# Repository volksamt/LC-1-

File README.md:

# LC-1-
Schematics for LC1 (Loud Card 1) miniature synthesizer/trigger generator

<h2> Copy </h2>
LC-1 is an armament designed to turn you into an Artiste-Agitator.

With its compact build, highly variable frequency range, and ferocious output power of 3Vpp, LC-1 is the perfect sonic infiltration tool
 for jam sessions and free-improvisation ensembles alike. 

It is crafted in alignment with Volksamt!’s artistic manifesto;

*
Hierarchy and harmony are shackles unto everything!
FcCUk order!
*

However, 
it would be absurd to send you to the fronts without sufficient training.
Thus;
 in the following pages you will find various scores
designed to boost your acumen.
Rehearse these well.

<h2> Technical </h2>

Lc1 is a mini touch reactive synthesizer designed as a small scale version of the much bigger light&sound installation |||||||| (wwww.volksamt.org/menagerie.html)

It is built around a simple schmitt trigger feedback oscillator design. 

Feel free to experiment with the capacitor values as everybodies skin resistance is different. Usually 22nF is a good stating point.

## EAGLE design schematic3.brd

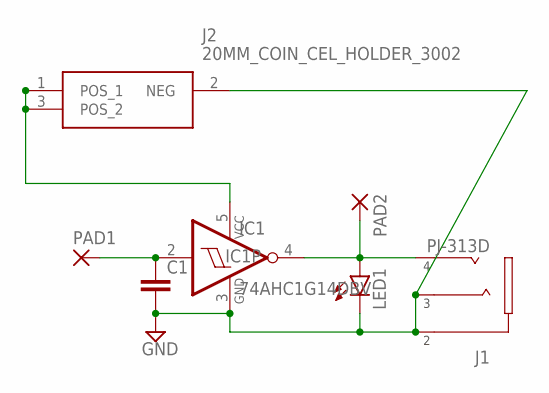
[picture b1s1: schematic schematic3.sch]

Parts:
C1: C-EUC0805; C0805
IC1: 74AHC1G14DBV; SOT23-5
J1: PJ-313D
J2: 20MM_COIN_CEL_HOLDER_3002; SMT_CELL_HOLDER
LED1: LEDCHIP-LED0805; CHIP-LED0805
PAD1, PAD2: SMD5; SMD2,54-5,08

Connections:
GND: C1.2, IC1.3 (GND), J1.2_1 (2), J1.2_2 (2), J1.3_1 (3), J1.3_2 (3), J2.2 (NEG), LED1.C
unnamed: C1.1, IC1.2 (I), PAD1.1
unnamed: IC1.5 (VCC), J2.1 (POS_1), J2.3 (POS_2)
unnamed: IC1.4 (O), J1.4_1 (4), J1.4_2 (4), LED1.A, PAD2.1

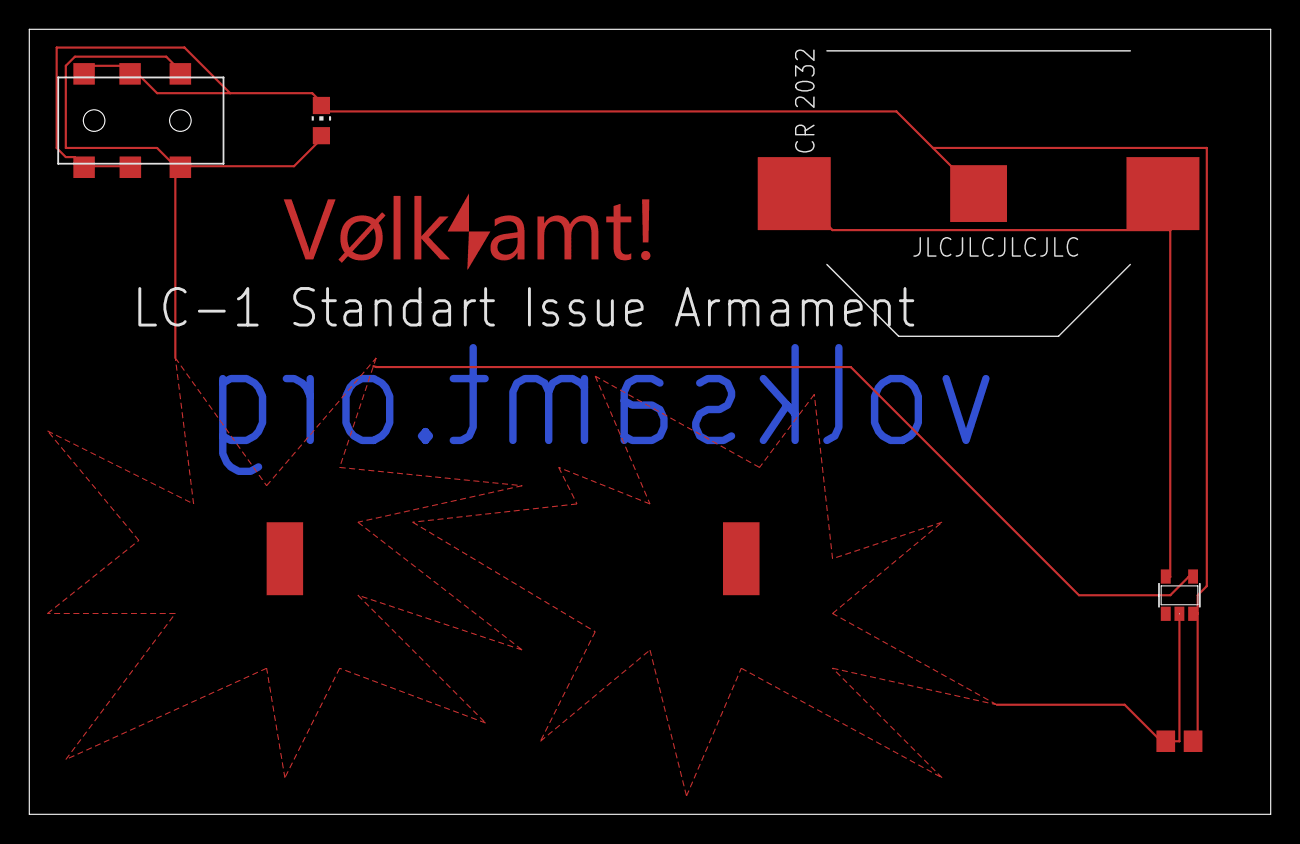
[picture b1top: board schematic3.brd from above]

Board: 2 copper layers, 86.4 x 54.6 mm, 7 parts (0 on the bottom side), 4 nets.
